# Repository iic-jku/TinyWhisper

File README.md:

# TinyWhisper: An Open-Source Fully-Integrated Multi-Mode Short-Wave Transmitter for Amateur Radio Applications in 130-nm CMOS

(c) 2025-2026 Simon Dorrer* (OE3SDE), Jonathan Hager** (DK7JH), Matthias Jung** (DL9MJ) and Harald Pretl*

*Institute for Integrated Circuits and Quantum Computing, Johannes Kepler University (JKU), Linz, Austria

**Computer Engineering, Julius-Maximilians-Universität, Würzburg, Germany

> [!IMPORTANT]
> This repository requires the [IIC-OSIC-TOOLS](https://github.com/iic-jku/IIC-OSIC-TOOLS) container with tag `2026.11` or later.

> [!TIP]
> This repository is based on the [ihp-sg13g2-ams-chip-template](https://github.com/iic-jku/ihp-sg13g2-ams-chip-template) template repository. For a better understanding of the folder structure, how to use the Makefiles, and how to implement your own designs, it is recommended to go through this [tutorial](https://iic-jku.github.io/ihp-sg13g2-ams-chip-template/index.html).

<p align="center">
  
  <br>
  <em>Die photo of the ihp-sg13cmos TinyWhisper ASIC (2mm x 2mm), taped out in March 2026.</em>
</p>

<p align="center">
  
  <br>
  <em>Chip render of the ihp-sg13cmos TinyWhisper ASIC (2mm x 2mm).</em>
</p>

<p align="center">
  
  <br>
  <em>Render of the TopMetal2 TinyWhisper logo, generated with the tool ArtistIC.</em>
</p>

## Video

Two videos of about 70 seconds introduce TinyWhisper to a general audience, one in English and one in German. Click a poster to play its video, or watch both in the [documentation](https://iic-jku.github.io/TinyWhisper/index.html#sec-video).

<table width="100%">
  <tr>
    <td align="center" width="50%">
      
      <br>
      <em>▶ English, 1:11</em>
    </td>
    <td align="center" width="50%">
      
      <br>
      <em>▶ German, 1:08</em>
    </td>
  </tr>
</table>

## Documentation

The full documentation of the TinyWhisper transmitter is available [here](https://iic-jku.github.io/TinyWhisper/index.html).

Moreover, look into the [`publications/`](https://github.com/iic-jku/TinyWhisper/tree/main/publications) folder for further information.

## Purpose

TinyWhisper demonstrates what is possible with current open-source tools and open-source PDKs, from system design to final tapeout, from packaging to PCB design, and even to a 3D-printed enclosure. It can also be used for:

- Ham radio courses
- University courses
- Regression tests of various open-source tools

## Chip Specifications

| Parameter           | Value                                                                             |
| ------------------- | --------------------------------------------------------------------------------- |
| Technology          | SKY130 \& IHP SG13CMOS (130 nm CMOS)                                              |
| Die Area            | 2000 × 2000 µm (4 mm²)                                                            |
| Core Area           | 1270 × 1270 µm (1.613 mm²)                                                        |
| Clock Frequency     | 56 MHz                                                                            |
| Core Supply Voltage | 1.5 V                                                                             |
| I/O Supply Voltage  | 3.3 V                                                                             |
| Total Pads          | 56 (clock, reset, 6 input, 9 output, 9 bidirectional, 8 analog, 7 VDD, 9 VSS, 3 IOVDD, 3 IOVSS) |
| Packaging           | QFN-48, the 9 VSS and 3 IOVSS pads are downbonded to the exposed pad (package ground) |
| Temperature Range   | -40 °C to +125 °C                                                                 |

## Overview

- Analog Front-End: IQ Modulator
    - 3rd-order multiple-feedback (MFB) low-pass filter
        - Butterworth
        - fc = 400 kHz
        - Barthelemy / Manfredini (B/M) inverter-based OTA
    - Passive CMOS voltage-mode mixer
        - Single-to-differential conversion circuit
        - Simple transmission-gate switch
- Digital Core
    - RISC-V CPU
        - SPI interface for external SRAM extension
        - I²C interface for external peripherals (I/O extender, display, keyboard, etc.)
        - UART interface for connection to PC / Raspberry Pi RP2040 + MicroPython
        - 8 × GPIOs (4 × inputs, one with external interrupt capability, and 4 × outputs)
    - 30-bit iterative CORDIC for sine / cosine generation
        - Adjustable amplitude
        - Adjustable fc, fm, and phim enable different modulation schemes
        - Frequency resolution: df = fclk / (OSR × 2^30), 1.63 mHz at OSR 32
        - Frequency word: fc = 2^30 × OSR × frequency / fclk (30 bit, signed)
    - Delta-Sigma modulator
        - OSR = 32 / 64 / 128 / 256
        - 1st / 2nd order
        - Inversion / exchange of the I/Q channel
    - 25% LO Generation for Mixer
        - LO = fclk / 2, 4, 8 or 16 (28, 14, 7 or 3.5 MHz)
        - Debugging modes (mixer TG always on / off → fully differential measurement of the MFB filter is possible)
    - Debugging features
        - Bidirectional pads: measure DSM / LO output or inject signals externally
        - Analog pads: inject analog IQ modulator signals externally

## Description

TinyWhisper is a compact WSPR transmitter realized with the ihp-sg13cmos PDK. The 2 mm x 2 mm chip operates at a core supply voltage of 1.5 V and an I/O supply voltage of 3.3 V. The chip is [packaged](https://github.com/iic-jku/TinyWhisper/tree/main/ihp130/packaging) in a QFN-48 package. The chip has 56 pads, and its 9 VSS and 3 IOVSS pads are downbonded to the exposed pad of the package. All documentation, presentations, design files, and future updates are publicly available [here](https://github.com/iic-jku/TinyWhisper/tree/main/publications). The block diagram is shown below. A render of the final chip layout is shown above, with the digital part placed on the left side of the chip and the analog part on the right. A custom logo on the topmost metal layer, generated with the tool [ArtistIC](https://arxiv.org/abs/2502.02626), is also shown above. The die photo at the top shows a fabricated chip of the March 2026 tapeout (`SoC4219`), with the TopMetal2 logo on top of the core.

<p align="center">
  
  <br>
  <em>Block diagram of the TinyWhisper ASIC and external RF circuitry.</em>
</p>

### Weak Signal Propagation Reporter

WSPR is a popular digital transmission scheme in amateur radio, specifically designed to study propagation conditions at low transmit power. WSPR transmits a short message containing the callsign, location, and transmit power using 4-FSK modulation (tone spacing 1.46 Hz, symbol duration 0.683 s). Thanks to strong forward error correction (rate 1/2), long ranges can be achieved even at very low transmit power levels (down to 10 mW). Receivers can decode WSPR signals down to -31 dB below the noise floor of a 2500 Hz channel. Received signals are reported to a central [database](https://www.wsprnet.org/drupal/wsprnet/map) via the internet, enabling global analysis of signal propagation.

### Digital Core

The heart of the digital core is a simple multi-cycle embedded processor based on a 32-bit RISC-V architecture running at a clock rate of 56 MHz. By using the RISC-V architecture, the CPU is directly compatible with common compilers, and programs can, for example, be written in C. The program is stored in an external SPI SRAM, from which the CPU fetches its instructions. For communication with peripherals, the chip features I2C and UART interfaces as well as digital GPIO pins that can be freely controlled.

An integrated 30-bit CORDIC algorithm generates the 4-FSK-modulated I/Q baseband signals according to the WSPR protocol. The phase increment of the CORDIC can be configured via software, allowing any frequency to be generated with a resolution of 1.63 mHz at an oversampling ratio of 32. This also enables compensation for frequency errors of the external crystal oscillator. Using a first- or second-order Delta-Sigma (DS) modulator with selectable oversampling (32, 64, 128, or 256), the parallel 30-bit data from the CORDIC is converted into a 1-bit signal that is passed directly to the analog front-end. Additionally, the digital core generates the LO frequencies listed in the table below by dividing the 56 MHz clock by 2, 4, 8 or 16, covering the most common shortwave bands: 28 MHz, 14 MHz, 7 MHz, and 3.5 MHz. The signal lands at the LO plus the IF only in the upper sideband, which the firmware has to select, see [errata TW-E03](https://github.com/iic-jku/TinyWhisper/blob/main/ihp130/doc/errata.md#tw-e03-default-iq-convention-transmits-the-lower-sideband).

| Band | RF Frequency  | LO Frequency | IF (CORDIC) |
| ---- | ------------- | ------------ | ----------- |
| 80m  | 3.568600 MHz  | 3.5 MHz      | 68.600 kHz  |
| 40m  | 7.038600 MHz  | 7 MHz        | 38.600 kHz  |
| 20m  | 14.095600 MHz | 14 MHz       | 95.600 kHz  |
| 10m  | 28.124600 MHz | 28 MHz       | 124.600 kHz |

### Analog Front-End

The analog front-end is an IQ modulator consisting of two third-order multiple-feedback (MFB) low-pass filters with a cutoff frequency of 400 kHz and a Butterworth characteristic. The amplifier core of the MFB filter is based on a Barthelemy / Manfredini (B/M) inverter-based OTA. Two passive voltage-mode mixers are driven by a 25% duty-cycle local oscillator and produce a single-ended RF output signal.

Integrated SPDT switches allow switching between the internal CORDIC/DSM signals and external analog inputs, enabling tests with an external function generator, among other uses.

Since the analog front-end is an IQ modulator, it supports not only WSPR but also other modulation schemes such as FT8, SSB, and CW. Hence, the title "TinyWhisper: An Open-Source Fully-Integrated Multi-Mode Short-Wave Transmitter for Amateur Radio Applications in 130-nm CMOS".

### Outlook

Bare dies of the March 2026 tapeout are back from fabrication, see the die photo at the top. The ASIC is just the beginning of a broader open-hardware project. The next step is to design a [PCB](https://github.com/iic-jku/TinyWhisper/tree/main/pcb) that includes all necessary external components: switchable bandpass filters for each RF band, an RF amplifier, a crystal oscillator as the clock source, external SRAM, voltage regulators for the various supply voltages, a display, controls, an SMA connector for the antenna, and a USB interface for configuration. The packaged chip will be soldered onto this board and then [characterized](https://github.com/iic-jku/TinyWhisper/tree/main/measurements).

Building on this PCB, a compact, 3D-printable [enclosure](https://github.com/iic-jku/TinyWhisper/tree/main/enclosure) is planned that accommodates the board together with a small battery and is robust enough for outdoor use during field tests and SOTA activations.

## ToDo List

The ToDo list can be found in [ToDo.md](https://github.com/iic-jku/TinyWhisper/tree/main/ToDo.md).

## Tapeouts

- [x] TinyWhisper Transmitter (Digital Core + IQ Modulator), IHP130: https://github.com/iic-jku/TinyWhisper/tree/main/ihp130/release and branch `IHP-TO-2026-03`
- [x] RISC-V CPU, GF180 wafer.space: https://github.com/iic-jku/gf180mcu-jku-projects
- [x] WSPR in Hardware without RISC-V CPU (see [archive](https://github.com/iic-jku/TinyWhisper/tree/main/sky130/macros/archive/verilog_TT_11-2025) folder), SKY130 Tiny Tapeout: https://tinytapeout.com/chips/ttsky25b/tt_um_cejmu_wspr
- [x] IQ Modulator, SKY130 Tiny Tapeout: https://tinytapeout.com/chips/ttsky25b/tt_um_TinyWhisper

## Directory Structure

The chip design itself lives in [`ihp130/`](https://github.com/iic-jku/TinyWhisper/tree/main/ihp130), which follows the layout of the [ihp-sg13g2-ams-chip-template](https://github.com/iic-jku/ihp-sg13g2-ams-chip-template). Its own [README](https://github.com/iic-jku/TinyWhisper/tree/main/ihp130/README.md) documents every Makefile target in detail.

<details>
<summary>Show Directory Structure</summary>

```text
📁 TinyWhisper/
├─ 📁 .github/
│  └─ 📁 workflows/
│     ├─ license-check.yml
│     ├─ quarto-publish.yml
│     └─ regression.yml
├─ 📁 doc/
│  ├─ 📁 fig/
│  │  ├─ 📁 funding/
│  │  │  ├─ iic-jku.pdf
│  │  │  ├─ iic-jku.svg
│  │  │  ├─ silicon-austria-labs-logo.pdf
│  │  │  └─ silicon-austria-labs-logo.svg
│  │  ├─ Makefile
│  │  ├─ TinyWhisper_architecture.drawio
│  │  ├─ TinyWhisper_architecture.svg
│  │  ├─ favicon.png
│  │  ├─ fec.svg
│  │  ├─ fec.tex
│  │  ├─ tinywhisper_blockdiagramm.png
│  │  ├─ tinywhisper_bondplan_white.png
│  │  ├─ tinywhisper_die.JPG
│  │  ├─ tinywhisper_top_black.png
│  │  ├─ tinywhisper_top_black_TM2.png
│  │  └─ tinywhisper_top_white.png
│  ├─ 📁 scripts/
│  │  └─ copy_sim_figures.ts
│  ├─ 📁 video/
│  │  ├─ tinywhisper_intro_de.jpg
│  │  ├─ tinywhisper_intro_de.mp4
│  │  ├─ tinywhisper_intro_en.jpg
│  │  └─ tinywhisper_intro_en.mp4
│  ├─ Makefile
│  ├─ _quarto.yml
│  ├─ dashboard.html
│  ├─ index.qmd
│  ├─ references.bib
│  ├─ requirements.txt
│  └─ styles.css
├─ 📁 enclosure/
│  └─ README.md
├─ 📁 ihp130/
│  ├─ 📁 doc/
│  ├─ 📁 flow/
│  │  ├─ 📁 artistic/
│  │  ├─ 📁 final/
│  │  ├─ 📁 librelane/
│  │  └─ 📁 logo/
│  ├─ 📁 ip/
│  │  ├─ 📁 sg13g2_io_custom/
│  │  ├─ 📁 sg13g2_ip__bondpad_70x70/
│  │  ├─ 📁 sg13g2_ip__rfpad_70x70/
│  │  ├─ 📁 sg13g2_ip__ce/
│  │  ├─ 📁 sg13g2_ip__ce_names/
│  │  ├─ 📁 sg13g2_ip__jku/
│  │  └─ 📁 sg13g2_ip__jku_names/
│  ├─ 📁 layout/
│  │  ├─ tinywhisper_top.gds.gz
│  │  └─ tinywhisper_top_logo_fill.gds.gz
│  ├─ 📁 macros/
│  │  ├─ 📁 coupled_resonator_lc_bpf/
│  │  ├─ 📁 iqmod/
│  │  ├─ 📁 riscv/
│  │  ├─ 📁 scripts/
│  │  ├─ Makefile
│  │  └─ README.md
│  ├─ 📁 netlist/
│  │  ├─ 📁 layout/
│  │  ├─ 📁 nl/
│  │  ├─ 📁 pex/
│  │  ├─ 📁 pnl/
│  │  ├─ 📁 schematic/
│  │  └─ 📁 spice/
│  ├─ 📁 packaging/
│  │  ├─ 📁 layout/
│  │  ├─ 📁 render/
│  │  ├─ 📁 scripts/
│  │  ├─ config.yaml
│  │  ├─ README.md
│  │  └─ result.md
│  ├─ 📁 release/
│  │  ├─ 📁 v.1.0.0/
│  │  │  ├─ 📁 doc/
│  │  │  │  └─ README.md
│  │  │  ├─ 📁 gds/
│  │  │  │  └─ SoC4219.gds.gz
│  │  │  └─ 📁 img/
│  │  │     ├─ tinywhisper_die_1.JPG
│  │  │     ├─ tinywhisper_die_2.JPG
│  │  │     ├─ tinywhisper_die_3.JPG
│  │  │     ├─ tinywhisper_top_black.png
│  │  │     └─ tinywhisper_top_white.png
│  │  └─ 📁 v.2.0.0/
│  │     ├─ 📁 gds/
│  │     │  └─ tinywhisper_top_logo_fill.gds.gz
│  │     ├─ 📁 img/
│  │     └─ 📁 netlist/
│  │        ├─ 📁 layout/
│  │        ├─ 📁 pnl/
│  │        └─ 📁 spice/
│  ├─ 📁 render/
│  │  ├─ 📁 blender/
│  │  └─ 📁 img/
│  │     ├─ tinywhisper_top_black.png
│  │     ├─ tinywhisper_top_librelane.png
│  │     └─ tinywhisper_top_white.png
│  ├─ 📁 rtl/
│  │  ├─ tinywhisper_core.sv
│  │  └─ tinywhisper_top.sv
│  ├─ 📁 schematic/
│  │  └─ 📁 xschem/
│  │     ├─ tinywhisper.sch
│  │     ├─ tinywhisper.sym
│  │     ├─ tinywhisper_top.sch
│  │     ├─ tinywhisper_top.sym
│  │     ├─ tinywhisper_top_pex.sym
│  │     └─ xschemrc
│  ├─ 📁 scripts/
│  │  ├─ add_logo_fill.sh
│  │  ├─ add_rectangle.py
│  │  └─ check_pex_ports.py
│  ├─ 📁 testbenches/
│  │  ├─ 📁 cocotb/
│  │  └─ 📁 xschem/
│  │     └─ 📁 plot_simulations/
│  ├─ 📁 verification/
│  │  ├─ 📁 drc/
│  │  ├─ 📁 lvs/
│  │  └─ 📁 reports/
│  ├─ Makefile
│  └─ README.md
├─ 📁 LICENSES/
│  ├─ Apache-2.0.txt
│  ├─ LicenseRef-EUROPRACTICE.txt
│  ├─ MIT.txt
│  └─ SHL-2.1.txt
├─ 📁 measurements/
│  └─ README.md
├─ 📁 pcb/
│  ├─ 📁 lib/
│  ├─ 📁 render/
│  ├─ README.md
│  ├─ tinywhisper_dev_board.kicad_pcb
│  ├─ tinywhisper_dev_board.kicad_pro
│  └─ tinywhisper_dev_board.kicad_sch
├─ 📁 publications/
│  ├─ EasterHegg_04042026.pdf
│  ├─ QSP100_Open-Source-Chip-Design.pdf
│  └─ README.md
├─ 📁 sky130/
│  └─ 📁 macros/
│     ├─ 📁 archive/
│     ├─ 📁 iqmod/
│     └─ 📁 riscv/
├─ 📁 software/
│  ├─ 📁 c_toolchain/
│  ├─ generate_tests.py
│  ├─ program_fpga_uart.py
│  ├─ README.md
│  ├─ test_wspr.py
│  └─ wspr.py
├─ .designinit
├─ .gitattributes
├─ .gitignore
├─ .gitmodules
├─ CITATION.cff
├─ LICENSE
├─ README.md
├─ REUSE.toml
└─ ToDo.md
```

</details>

## Cite This Work

```
@software{2026_TinyWhisper,
	author = {Dorrer, Simon and Hager, Jonathan and Jung, Matthias and Pretl, Harald},
	month = apr,
    year = {2026},
	title = {{GitHub Repository for TinyWhisper: An Open-Source Fully-Integrated Multi-Mode Short-Wave Transmitter for Amateur Radio Applications in 130-nm CMOS}},
	url = {https://github.com/iic-jku/TinyWhisper},
	doi = {10.5281/zenodo.20004085}
}
```

## Acknowledgements

Thanks to Chance Reimer for providing an open source [I2C module](https://github.com/chance189/I2C_Master) and to Ben Marshall for providing a [UART implementation](https://github.com/ben-marshall/uart).

This project is funded by the JKU/SAL [IWS Lab](https://research.jku.at/de/projects/jku-lit-sal-intelligent-wireless-systems-lab-iws-lab/), a collaboration of [Johannes Kepler University](https://jku.at) and [Silicon Austria Labs](https://silicon-austria-labs.com).

<table width="100%">
  <tr>
    <td align="left" width="50%">
      
    </td>
    <td align="right" width="50%">
      
    </td>
  </tr>
</table>

## License

Licensed under the **Solderpad Hardware License v2.1**, see [`LICENSE`](LICENSE).

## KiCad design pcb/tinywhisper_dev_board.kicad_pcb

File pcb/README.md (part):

# TinyWhisper dev board

KiCad 10 project of the bring-up board for SoC4219, the first TinyWhisper silicon, in its open-molded QFN-48.
Revision 0.1 covers the digital side completely and gives the RF side debug access only: the four RF outputs joined into a 1 kΩ load and an SMA for a spectrum analyzer, with no band-pass filter, no band switching and no power amplifier.
Every board condition of [`ihp130/doc/errata.md`](../ihp130/doc/errata.md) is built in and cited as `TW-Exx`. [`measurements/README.md`](../measurements/README.md) is the bring-up protocol for this board.

## Block diagram

The sections below give each block's parts and values. `Exx` in the diagram is the errata entry `TW-Exx`.

## Files

| File | Contents |
| --- | --- |
| `tinywhisper_dev_board.kicad_pro` | Project: net classes (`Default`, `Power`), design rules, track and via presets |
| `tinywhisper_dev_board.kicad_sch` | Root sheet: chip, decoupling, straps for the two bond plans, mechanics |
| `power.kicad_sch` | 5 V from the Pico, 3.3 V board rail, `IOVDD` with its supervisor, `VDD` |
| `host.kicad_sch` | Raspberry Pi Pico H, 56 MHz clock, reset flip-flop, UART, links to the chip |
| `memory.kicad_sch` | PSRAM and the chip-side bus buffers |
| `user.kicad_sch` | Buttons, LEDs, I2C, GPIO header, monitor pads |
| `analog.kicad_sch` | External analog inputs, RF debug output |
| `tinywhisper_dev_board.kicad_pcb` | Board, revision 0.1 |
| `tinywhisper_dev_board.kicad_dru` | Custom rules: the stricter value of JLCPCB and Aisler per rule, plus house rules |
| `lib/` | Chip symbol, Pico H symbol, QFN-48 land pattern, Pico socket, SMA and the board-only logos |
| `render/` | Renders of the board |
| `block_diagram.svg` | Block diagram of revision 0.1, drawn separately from the schematic: update it when a block changes |

Stock parts use the KiCad 10 libraries, and their 3D models resolve through `${KICAD10_3DMODEL_DIR}`.

## Chip

| Item | Value |
| --- | --- |
| Package | QP Technologies `QP-QFN48-7MM-0.50MM` (dwg 500363 rev A), the EUROPRACTICE `OP_QFN48`: 7 × 7 mm, 0.5 mm pitch, 0.23 mm leads, 5.1 mm exposed pad |
| Land pattern | 0.25 mm lands from 3.0 to 4.05 mm off the centre (0.55 mm toe for an iron), 5.1 mm exposed pad with a 1.0 mm plated hole for soldering from the bottom |
| Ground | The exposed pad is the only ground of the die: all 9 `VSS` and 3 `IOVSS` pads are downbonded to the paddle, and the leads 15, 27, 34 and 46 are bonded to it ([`ihp130/packaging/config.yaml`](../ihp130/packaging/config.yaml)). Eight vias in the pad tie it to all four layers. |
| Orientation | Turned by 270°: pins 1 to 12 (clock, reset, SPI, I2C, UART) face the Pico and the PSRAM, pins 25 to 36 (analog inputs, RF) face the RF SMA |
| Decoupling | 100 nF 0603 per supply pin on the bottom side, `C101` to `C107` for the `VDD` pins 8, 14, 20, 28, 33, 41, 47 and `C108` to `C110` for the `IOVDD` pins 7, 13, 48. Each supply pin has a fixed escape on `F.Cu` to a via in the supply pad of its own capacitor, 4.75 mm from the chip centre, and each capacitor's ground pad a via on the same axis. Pins 7 and 47 sit next to the supply pins 8 and 48, so their escapes run past those vias to `C108` and `C107` at 9.2 mm. Pin 14 reaches `VDD` through the strap `R101`, with `C102` beside it. |
| Escapes | Every other signal pin has a straight 0.25 mm stub out to 5.3 mm from the centre, so the autorouter starts outside the ring of supply vias. The vias on the pin axes are 0.45 mm with a 0.25 mm drill and the escapes 0.25 mm wide near the chip, so a neighbouring escape passes a via at the 0.15 mm clearance. |

Pins 14 and 15 were swapped in the bond plan of 2026-11-11 (TW-D03). The board straps both variants:

| Bond plan | Pin 14 | Pin 15 | Fit |
| --- | --- | --- | --- |
| 2026-11-11 (`ihp130/packaging/result.md`, default) | `VDD` | `IOVSS` lead to the cavity | `R101`, `R103` |
| Before 2026-11-11 | `IOVSS` | `VDD` | `R102`, `R104` instead |

Check one loose part before soldering: pin 15 against the exposed pad reads about 0 Ω for the plan of 2026-11-11. Step 1 of [`measurements/README.md`](../measurements/README.md) has the full check.

## Supplies

| Rail | Source | Load |
| --- | --- | --- |
| `+5V` | Pico `VBUS` (pin 40) through the ferrite `FB201`, so the Pico's USB powers the board | `U201` |
| `+3V3` | `U201` AP2112K-3.3, 600 mA | Pico interface, PSRAM, bus buffers, oscillator, reset flip-flop, OLED, `IOVDD`, `VDD` regulator |
| `IOVDD` | `+3V3` through the current jumper `JP201`, voltage header `J201` | Chip I/O ring (3 pins), the pull-ups on chip inputs |
| `VDD` | `U203` LP5907MFX-1.5 from `+3V3`, through the current jumper `JP202`, voltage header `J202` | Chip core (7 pins): CPU and IQ modulator share it (TW-E28) |

Sequencing (TW-E31): the supervisor `U202` (TPS3839K33) raises `PG_IO` 200 ms after `IOVDD` exceeds 2.93 V. `PG_IO` enables `U203`, so `VDD` follows `IOVDD`, and the LP5907 output discharge pulls `VDD` down first when `IOVDD` drops. `PG_IO` also clears the reset flip-flop, so `rst_n` stays low without `IOVDD`.
The LP5907 sees 6.4 µF on its output (`C208`, `C209` and the seven `VDD` decoupling capacitors), within its 10 µF limit.

Pull `JP201` or `JP202` to measure a current with an ammeter, or to feed a current-limited bench supply into pin 2 of the jumper (the chip side) with `GND` on pin 2 of `J201` or `J202`. With the bench supply, bring up `IOVDD` before `VDD`.

## Host

A Raspberry Pi Pico H (RP2040) on two 1x20 sockets loads the program, owns reset and the PSRAM bus, and bridges USB to the chip's UART, as the RP2040 does on pico-ice.

| Pico | Net | Function |
| --- | --- | --- |
| `GP0` | `UART_RX` through `R310` 1 kΩ | Chip `rx` (pin 11), 10 kΩ pull-up `R311` to `IOVDD` (TW-E29) |
| `GP1` | `UART_TX` through `R312` 1 kΩ | Chip `tx` (pin 12) |
| `GP2` | `BUS_PICO`, 10 kΩ pull-up `R326` | High: the Pico owns the PSRAM and the chip-side buffers are off (TW-E02) |
| `GP3` | `RST_REQ_N` through `R307` 1 kΩ, 10 kΩ pull-down `R308` | Reset request into the flip-flop, low until the firmware releases it |
| `GP4`, `GP5` | `SDA`, `SCL` through `R321`, `R322` (not fitted) | I2C sniffer, the chip stays the only master (TW-E14) |
| `GP6` to `GP9` | `gpio_in[0..3]` through 1 kΩ (`R313` to `R316`) | Drive the chip inputs, `gpio_in[0]` is the external interrupt (TW-E24) |
| `GP10` to `GP13` | `gpio_out[0..3]` through 1 kΩ (`R317` to `R320`) | Read the chip outputs |
| `GP14` | `CLK_OE`, 10 kΩ pull-up `R301` | Oscillator enable, on while the pin is an input |
| `GP16` to `GP19` | `PSRAM_SO` (`R411`), `PSRAM_CE_N` (`R408`), `PSRAM_SCLK` (`R409`), `PSRAM_SI` (`R410`), 100 Ω each | SPI0 to the PSRAM: MISO, CS, SCK, MOSI |
| `GP26` | `VDD` through `R323` 1 kΩ | ADC readback of `VDD` |
| `GP27` | `IOVDD / 2` (`R324`, `R325`) | ADC readback of `IOVDD` |
| `GP15`, `GP20` to `GP22`, `GP28` | `J303` | Spare |
| `RUN` | `SW301` | Pico reset |

Loading order: with `BUS_PICO` high the Pico writes the program into the PSRAM over SPI0 (150 µs after power-up at the earliest), checks `VDD` on `GP26`, sets `BUS_PICO` low and raises `RST_REQ_N`. The flip-flop then releases `rst_n` on the next rising clock edge.

## Clock and reset

- `X301` is a 56 MHz SiT8008 CMOS oscillator at 3.3 V (programmable family, any frequency to order). `R304` (0 Ω, fitted) selects it. For a generator, fit `R305` instead and drive the SMA `J301` with a 3.3 V CMOS square wave. `R303` (49.9 Ω, not fitted) terminates a generator that needs it.
- The clock passes `R306` (33 Ω) to pin 1 and clocks the reset flip-flop `U301` (74AUP1G74 at 3.3 V, clock input high at 2.0 V or more). On 10 m the clock duty sets the I/Q balance (TW-E27): trim it with a generator on `J301`.
- `U301` releases `rst_n` (through `R309`, 33 Ω) synchronous to the clock (TW-E25), clears it while `PG_IO` is low (TW-E31), and `SW302` (RESET) pulls its D input low.
- Test points: `TP301` on `CLK` at the chip, `TP302` on `RST_N`.

## Memory

The CPU fetches from `U401`, an APS6404L-3SQR 64 Mbit SPI PSRAM at 3.3 V.
The chip's `si`, `sclk` and `sram_ce` drive even in reset and `sclk` runs at 28 MHz without pause (TW-E02), so they reach the PSRAM through the tri-state buffers `U403` (`si`), `U402` (`sclk`) and the inverting `U404` (`sram_ce` is active high, TW-E01), all enabled while `BUS_PICO` is low. `R401` keeps `CE#` high while nobody drives it, and `R405` keeps the inverter input low with the chip unpowered.
The series resistors `R402` to `R404` and `R406` (33 Ω) sit at the chip pins, and `R407` pulls `so` up (TW-E29).

## User I/O

| Part | Function |
| --- | --- |
| `SW501` to `SW504` | Buttons on `gpio_in[0..3]`, 1 kΩ to `IOVDD` (`R513` to `R516`), 10 kΩ pull-downs (`R501` to `R504`, TW-E29) |
| `D501` to `D504` | LEDs on `gpio_out[0..3]` through 1 kΩ (`R505` to `R508`) |
| `J501` | I2C display module: 1 `GND`, 2 `+3V3`, 3 `SCL`, 4 `SDA`. The chip drives `SDA` high push-pull, so 100 Ω in series (`R509`, `R510`) and 4.7 kΩ pull-ups to `IOVDD` (`R511`, `R512`). Fast-mode slaves that never stretch the clock (TW-E14, TW-E15). |
| `J302` | UART: 1 `tx` (chip output), 2 `rx` (chip input), 3 `GND`. The host sends 2 stop bits (TW-E07). |
| `J303` | Spare Pico pins: 1 `+3V3`, 2 `GP15`, 3 `GP20`, 4 `GP21`, 5 `GP22`, 6 `GP28`, 7 `GND` |

`J502` (GPIO) and `J503` (monitor pads) have the signals on the odd pins and `GND` on every even pin:

| Pin | `J502` | `J503` |
| --- | --- | --- |
| 1 | `gpio_in[0]` | `lo_I` (pin 38) |
| 3 | `gpio_in[1]` | `lo_Ix` (pin 37) |
| 5 | `gpio_in[2]` | `lo_Q` (pin 23) |
| 7 | `gpio_in[3]` | `lo_Qx` (pin 24) |
| 9 | `gpio_out[0]` through 100 Ω | `ds_I_p` (pin 40) |
| 11 | `gpio_out[1]` through 100 Ω | `ds_I_n` (pin 39) |
| 13 | `gpio_out[2]` through 100 Ω | `ds_Q_p` (pin 21) |
| 15 | `gpio_out[3]` through 100 Ω | `ds_Q_n` (pin 22) |

The eight monitor pads drive 30 mA at the LO rate whenever the internal LO runs (TW-E26). Each reaches `J503` through 100 Ω at the chip (`R517` to `R524`) and has a 100 kΩ pull-down at the pin (`R525` to `R532`), because the reset value of `FREQ_STATUS` makes them inputs (TW-E04).

## Analog inputs and RF debug output

- `J601` brings out the four external analog inputs (1 `vinp_I`, 3 `vinn_I`, 5 `vinp_Q`, 7 `vinn_Q`, even pins `GND`). Each passes 1 kΩ (`R601` to `R604`) and is biased to `VCM` = 0.75 V through 100 kΩ (`R605` to `R608`, divider `R609`, `R610` from `VDD`). Keep them within 0 to 1.5 V and never drive them with the chip unpowered: their clamps go to `IOVDD` (TW-E30).
- The four RF outputs (pins 29 to 32) are joined through the 0 Ω links `R611` to `R614` into `RF_SUM` (TW-E03, test point `TP601`). `C602` (100 nF) blocks their 0.75 V DC level (TW-E30), and `R615` (953 Ω) feeds the end-launch SMA `J602`. With a 50 Ω analyzer the outputs see 1003 Ω, and the analyzer reads 26.0 dB below the voltage at `RF_SUM`. Remove three links to measure one output alone.
- There is no filter on this board: the switching mixer puts power at odd LO harmonics. Use `J602` only into an analyzer or through an external low-pass filter.

## Assembly

All passives are 0603 or larger and all ICs leaded or with a land toe (SOT-23, SSOP-8, SOIC-8, the QFN-48 with extended lands), so the board can be soldered by hand. Connectors, buttons and test points are through-hole.
The QFN-48 exposed pad is soldered from the bottom through its 1.0 mm hole, or on a hot plate. The decoupling capacitors `C101` to `C110` sit on the bottom side under the chip, so solder the chip first.
The Pico H sits on two 1x20 sockets (Sullins PPTC201LFBN-RC), so it can be replaced and its own pins stay free.

## Markings

- Layer marker below the spare Pico header: `TOP` (`F.Cu`) and `2` (`In1.Cu`) read from the top, `3` (`In2.Cu`) and `BOT` (`B.Cu`), mirrored, from the bottom, in rule areas that forbid only the pour.
- Write-on field for the part number above the title.
- Every connector, jumper, button and test point is named by function. The supply jumpers read `IOVDD I` and `VDD I`, their voltage headers `U`, and `TP601` (`RF_SUM`) reads `RF`.
- JKU, ESD and WEEE logos on the bottom silkscreen, as board-only footprints (no symbol, not in the BOM or the position files).

## Fabrication

The board fits both JLCPCB and Aisler on one rule set, as the SPARX probe board: per rule the stricter value of the two.

| Rule | Value |
| --- | --- |
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
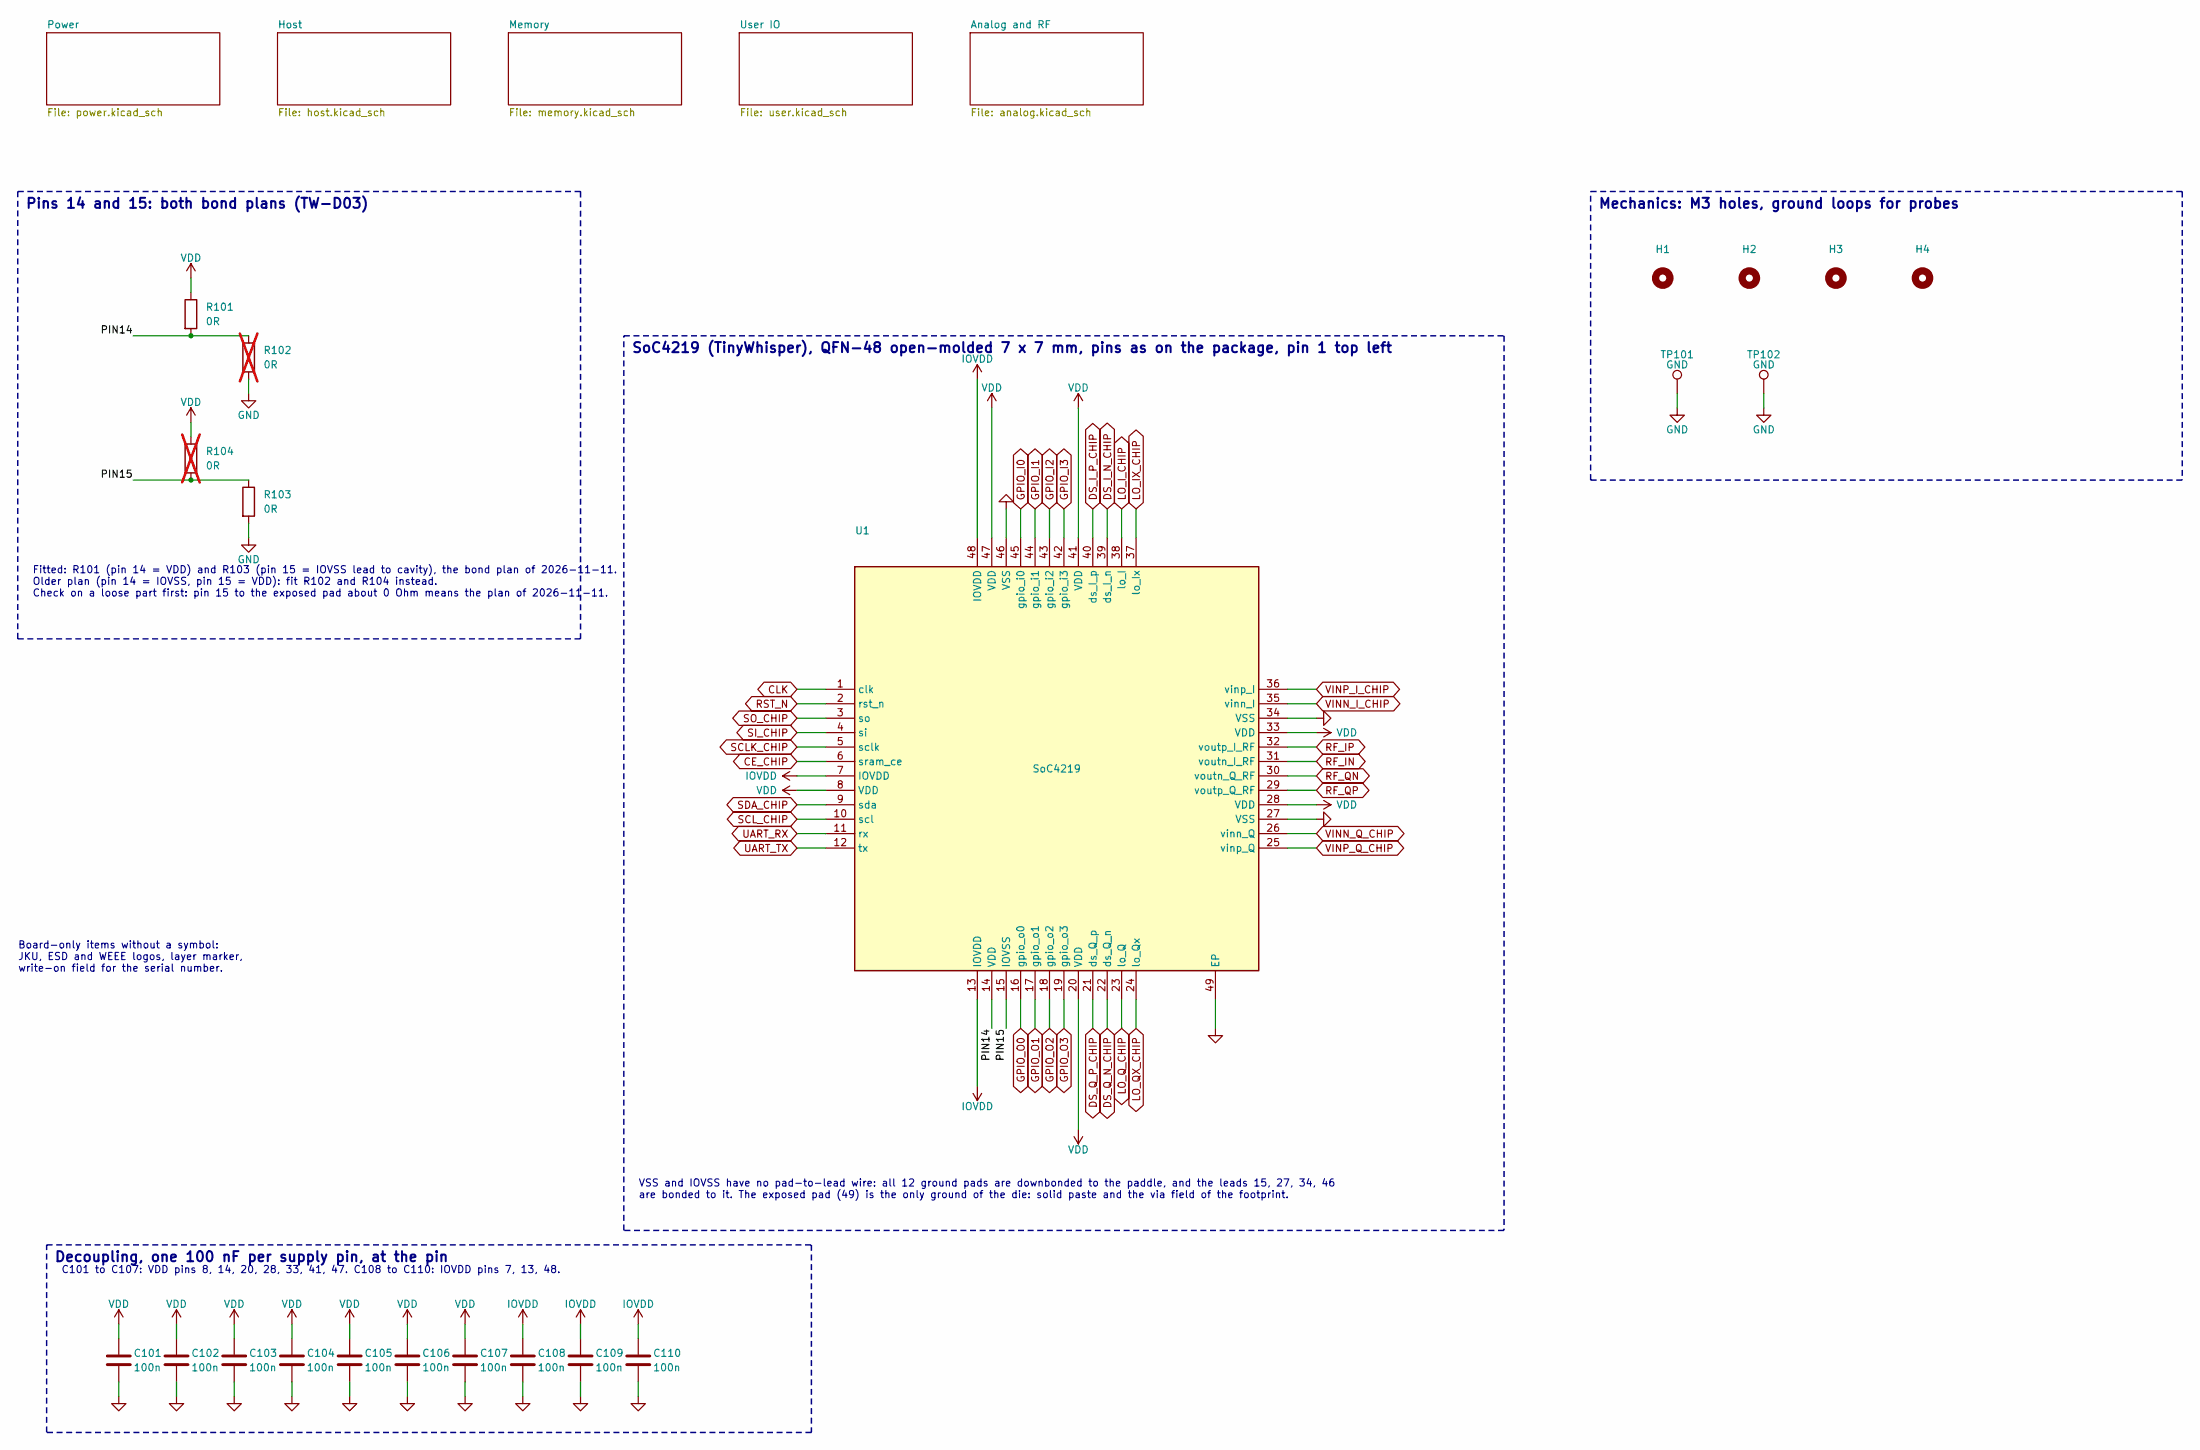
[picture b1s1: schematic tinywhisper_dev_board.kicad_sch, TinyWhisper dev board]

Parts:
C101, C102, C103, C104, C105, C106, C107, C108, C109, C110: 100n; C_0603_1608Metric_Pad1.08x0.95mm_HandSolder; MPN CL10B104KB8NNNC
H1, H2, H3, H4: MountingHole_M3; MountingHole_3.2mm_M3
R101, R103: 0R; R_0603_1608Metric_Pad0.98x0.95mm_HandSolder; MPN RC0603JR-070RL
R102, R104: 0R; R_0603_1608Metric_Pad0.98x0.95mm_HandSolder; MPN RC0603JR-070RL; not fitted
TP101, TP102: GND; TestPoint_Keystone_5000-5004_Miniature; MPN 5000
U1: SoC4219; QFN-48-1EP_7x7mm_P0.5mm_EP5.1x5.1mm_OpenPak_HandSolder

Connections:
/PIN14: R101.2, R102.1, U1.14 (VDD)
/PIN15: R103.1, R104.2, U1.15 (IOVSS)
CE_CHIP: U1.6 (sram_ce); also elsewhere on the board
CLK: U1.1 (clk); also elsewhere on the board
DS_I_N_CHIP: U1.39 (ds_I_n); also elsewhere on the board
DS_I_P_CHIP: U1.40 (ds_I_p); also elsewhere on the board
DS_Q_N_CHIP: U1.22 (ds_Q_n); also elsewhere on the board
DS_Q_P_CHIP: U1.21 (ds_Q_p); also elsewhere on the board
GND: C101.2, C102.2, C103.2, C104.2, C105.2, C106.2, C107.2, C108.2, C109.2, C110.2, R102.2, R103.2, TP101.1, TP102.1, U1.27 (VSS), U1.34 (VSS), U1.46 (VSS), U1.49 (EP); also elsewhere on the board
GPIO_I0: U1.45 (gpio_i0); also elsewhere on the board
GPIO_I1: U1.44 (gpio_i1); also elsewhere on the board
GPIO_I2: U1.43 (gpio_i2); also elsewhere on the board
GPIO_I3: U1.42 (gpio_i3); also elsewhere on the board
GPIO_O0: U1.16 (gpio_o0); also elsewhere on the board
GPIO_O1: U1.17 (gpio_o1); also elsewhere on the board
GPIO_O2: U1.18 (gpio_o2); also elsewhere on the board
GPIO_O3: U1.19 (gpio_o3); also elsewhere on the board
IOVDD: C108.1, C109.1, C110.1, U1.7 (IOVDD), U1.13 (IOVDD), U1.48 (IOVDD); also elsewhere on the board
LO_IX_CHIP: U1.37 (lo_Ix); also elsewhere on the board
LO_I_CHIP: U1.38 (lo_I); also elsewhere on the board
LO_QX_CHIP: U1.24 (lo_Qx); also elsewhere on the board
LO_Q_CHIP: U1.23 (lo_Q); also elsewhere on the board
RF_IN: U1.31 (voutn_I_RF); also elsewhere on the board
RF_IP: U1.32 (voutp_I_RF); also elsewhere on the board
RF_QN: U1.30 (voutn_Q_RF); also elsewhere on the board
RF_QP: U1.29 (voutp_Q_RF); also elsewhere on the board
RST_N: U1.2 (rst_n); also elsewhere on the board
SCLK_CHIP: U1.5 (sclk); also elsewhere on the board
SCL_CHIP: U1.10 (scl); also elsewhere on the board
SDA_CHIP: U1.9 (sda); also elsewhere on the board
SI_CHIP: U1.4 (si); also elsewhere on the board
SO_CHIP: U1.3 (so); also elsewhere on the board
UART_RX: U1.11 (rx); also elsewhere on the board
UART_TX: U1.12 (tx); also elsewhere on the board
VDD: C101.1, C102.1, C103.1, C104.1, C105.1, C106.1, C107.1, R101.1, R104.1, U1.8 (VDD), U1.20 (VDD), U1.28 (VDD), U1.33 (VDD), U1.41 (VDD), U1.47 (VDD); also elsewhere on the board
VINN_I_CHIP: U1.35 (vinn_I); also elsewhere on the board
VINN_Q_CHIP: U1.26 (vinn_Q); also elsewhere on the board
VINP_I_CHIP: U1.36 (vinp_I); also elsewhere on the board
VINP_Q_CHIP: U1.25 (vinp_Q); also elsewhere on the board

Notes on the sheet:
SoC4219 (TinyWhisper), QFN-48 open-molded 7 x 7 mm, pins as on the package, pin 1 top left
VSS and IOVSS have no pad-to-lead wire: all 12 ground pads are downbonded to the paddle, and the leads 15, 27, 34, 46 are bonded to it. The exposed pad (49) is the only ground of the die: solid paste and the via field of the footprint.
Pins 14 and 15: both bond plans (TW-D03)
Fitted: R101 (pin 14 = VDD) and R103 (pin 15 = IOVSS lead to cavity), the bond plan of 2026-11-11. Older plan (pin 14 = IOVSS, pin 15 = VDD): fit R102 and R104 instead. Check on a loose part first: pin 15 to the exposed pad about 0 Ohm means the plan of 2026-11-11.
Decoupling, one 100 nF per supply pin, at the pin
C101 to C107: VDD pins 8, 14, 20, 28, 33, 41, 47. C108 to C110: IOVDD pins 7, 13, 48.
Mechanics: M3 holes, ground loops for probes
Board-only items without a symbol: JKU, ESD and WEEE logos, layer marker, write-on field for the serial number.

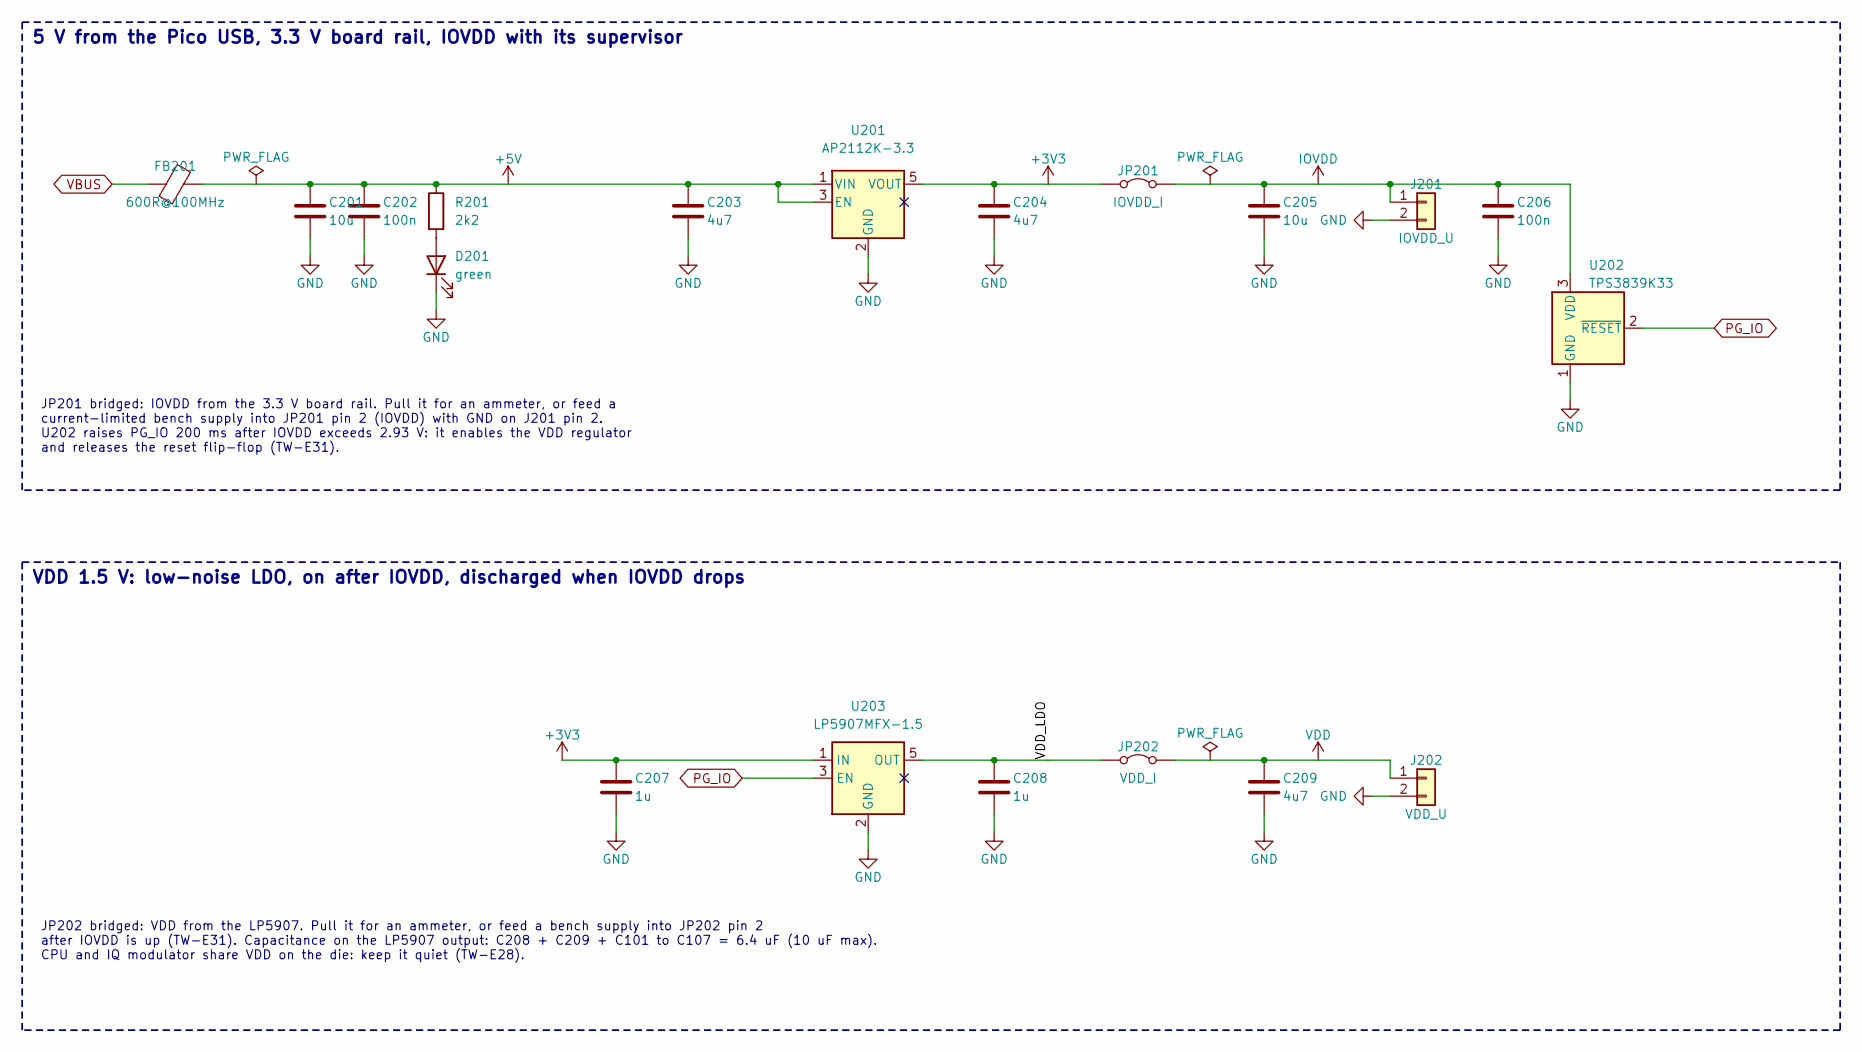
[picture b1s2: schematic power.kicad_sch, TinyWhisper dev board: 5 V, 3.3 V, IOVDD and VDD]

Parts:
C201: 10u; C_1206_3216Metric_Pad1.33x1.80mm_HandSolder; MPN GRM31CR71E106KA12L
C202, C206: 100n; C_0603_1608Metric_Pad1.08x0.95mm_HandSolder; MPN CL10B104KB8NNNC
C203, C204, C209: 4u7; C_0805_2012Metric_Pad1.18x1.45mm_HandSolder; MPN CL21B475KOFNNNE
C205: 10u; C_0805_2012Metric_Pad1.18x1.45mm_HandSolder; MPN CL21A106KOQNNNE
C207, C208: 1u; C_0603_1608Metric_Pad1.08x0.95mm_HandSolder; MPN CL10B105KO8NNNC
D201: green; LED_0603_1608Metric_Pad1.05x0.95mm_HandSolder; MPN APT1608LZGCK
FB201: 600R@100MHz; L_0603_1608Metric_Pad1.05x0.95mm_HandSolder; MPN BLM18KG601SN1D
J201: IOVDD_U; PinHeader_1x02_P2.54mm_Vertical
J202: VDD_U; PinHeader_1x02_P2.54mm_Vertical
JP201: IOVDD_I; PinHeader_1x02_P2.54mm_Vertical
JP202: VDD_I; PinHeader_1x02_P2.54mm_Vertical
R201: 2k2; R_0603_1608Metric_Pad0.98x0.95mm_HandSolder; MPN RC0603FR-072K2L
U201: AP2112K-3.3; SOT-23-5; MPN AP2112K-3.3TRG1
U202: TPS3839K33; SOT-23; MPN TPS3839K33DBZR
U203: LP5907MFX-1.5; SOT-23-5; MPN LP5907MFX-1.5/NOPB

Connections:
+3V3: C204.1, C207.1, JP201.1 (A), U201.5 (VOUT), U203.1 (IN); also elsewhere on the board
+5V: C201.1, C202.1, C203.1, FB201.2, R201.1, U201.1 (VIN), U201.3 (EN)
/Power/VDD_LDO: C208.1, JP202.1 (A), U203.5 (OUT)
GND: C201.2, C202.2, C203.2, C204.2, C205.2, C206.2, C207.2, C208.2, C209.2, D201.1 (K), J201.2, J202.2, U201.2 (GND), U202.1 (GND), U203.2 (GND); also elsewhere on the board
IOVDD: C205.1, C206.1, J201.1, JP201.2 (B), U202.3 (VDD); also elsewhere on the board
unnamed: D201.2 (A), R201.2
PG_IO: U202.2 (~RESET), U203.3 (EN); also elsewhere on the board
VBUS: FB201.1; also elsewhere on the board
VDD: C209.1, J202.1, JP202.2 (B); also elsewhere on the board

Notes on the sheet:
5 V from the Pico USB, 3.3 V board rail, IOVDD with its supervisor
JP201 bridged: IOVDD from the 3.3 V board rail. Pull it for an ammeter, or feed a current-limited bench supply into JP201 pin 2 (IOVDD) with GND on J201 pin 2. U202 raises PG_IO 200 ms after IOVDD exceeds 2.93 V: it enables the VDD regulator and releases the reset flip-flop (TW-E31).
VDD 1.5 V: low-noise LDO, on after IOVDD, discharged when IOVDD drops
JP202 bridged: VDD from the LP5907. Pull it for an ammeter, or feed a bench supply into JP202 pin 2 after IOVDD is up (TW-E31). Capacitance on the LP5907 output: C208 + C209 + C101 to C107 = 6.4 uF (10 uF max). CPU and IQ modulator share VDD on the die: keep it quiet (TW-E28).

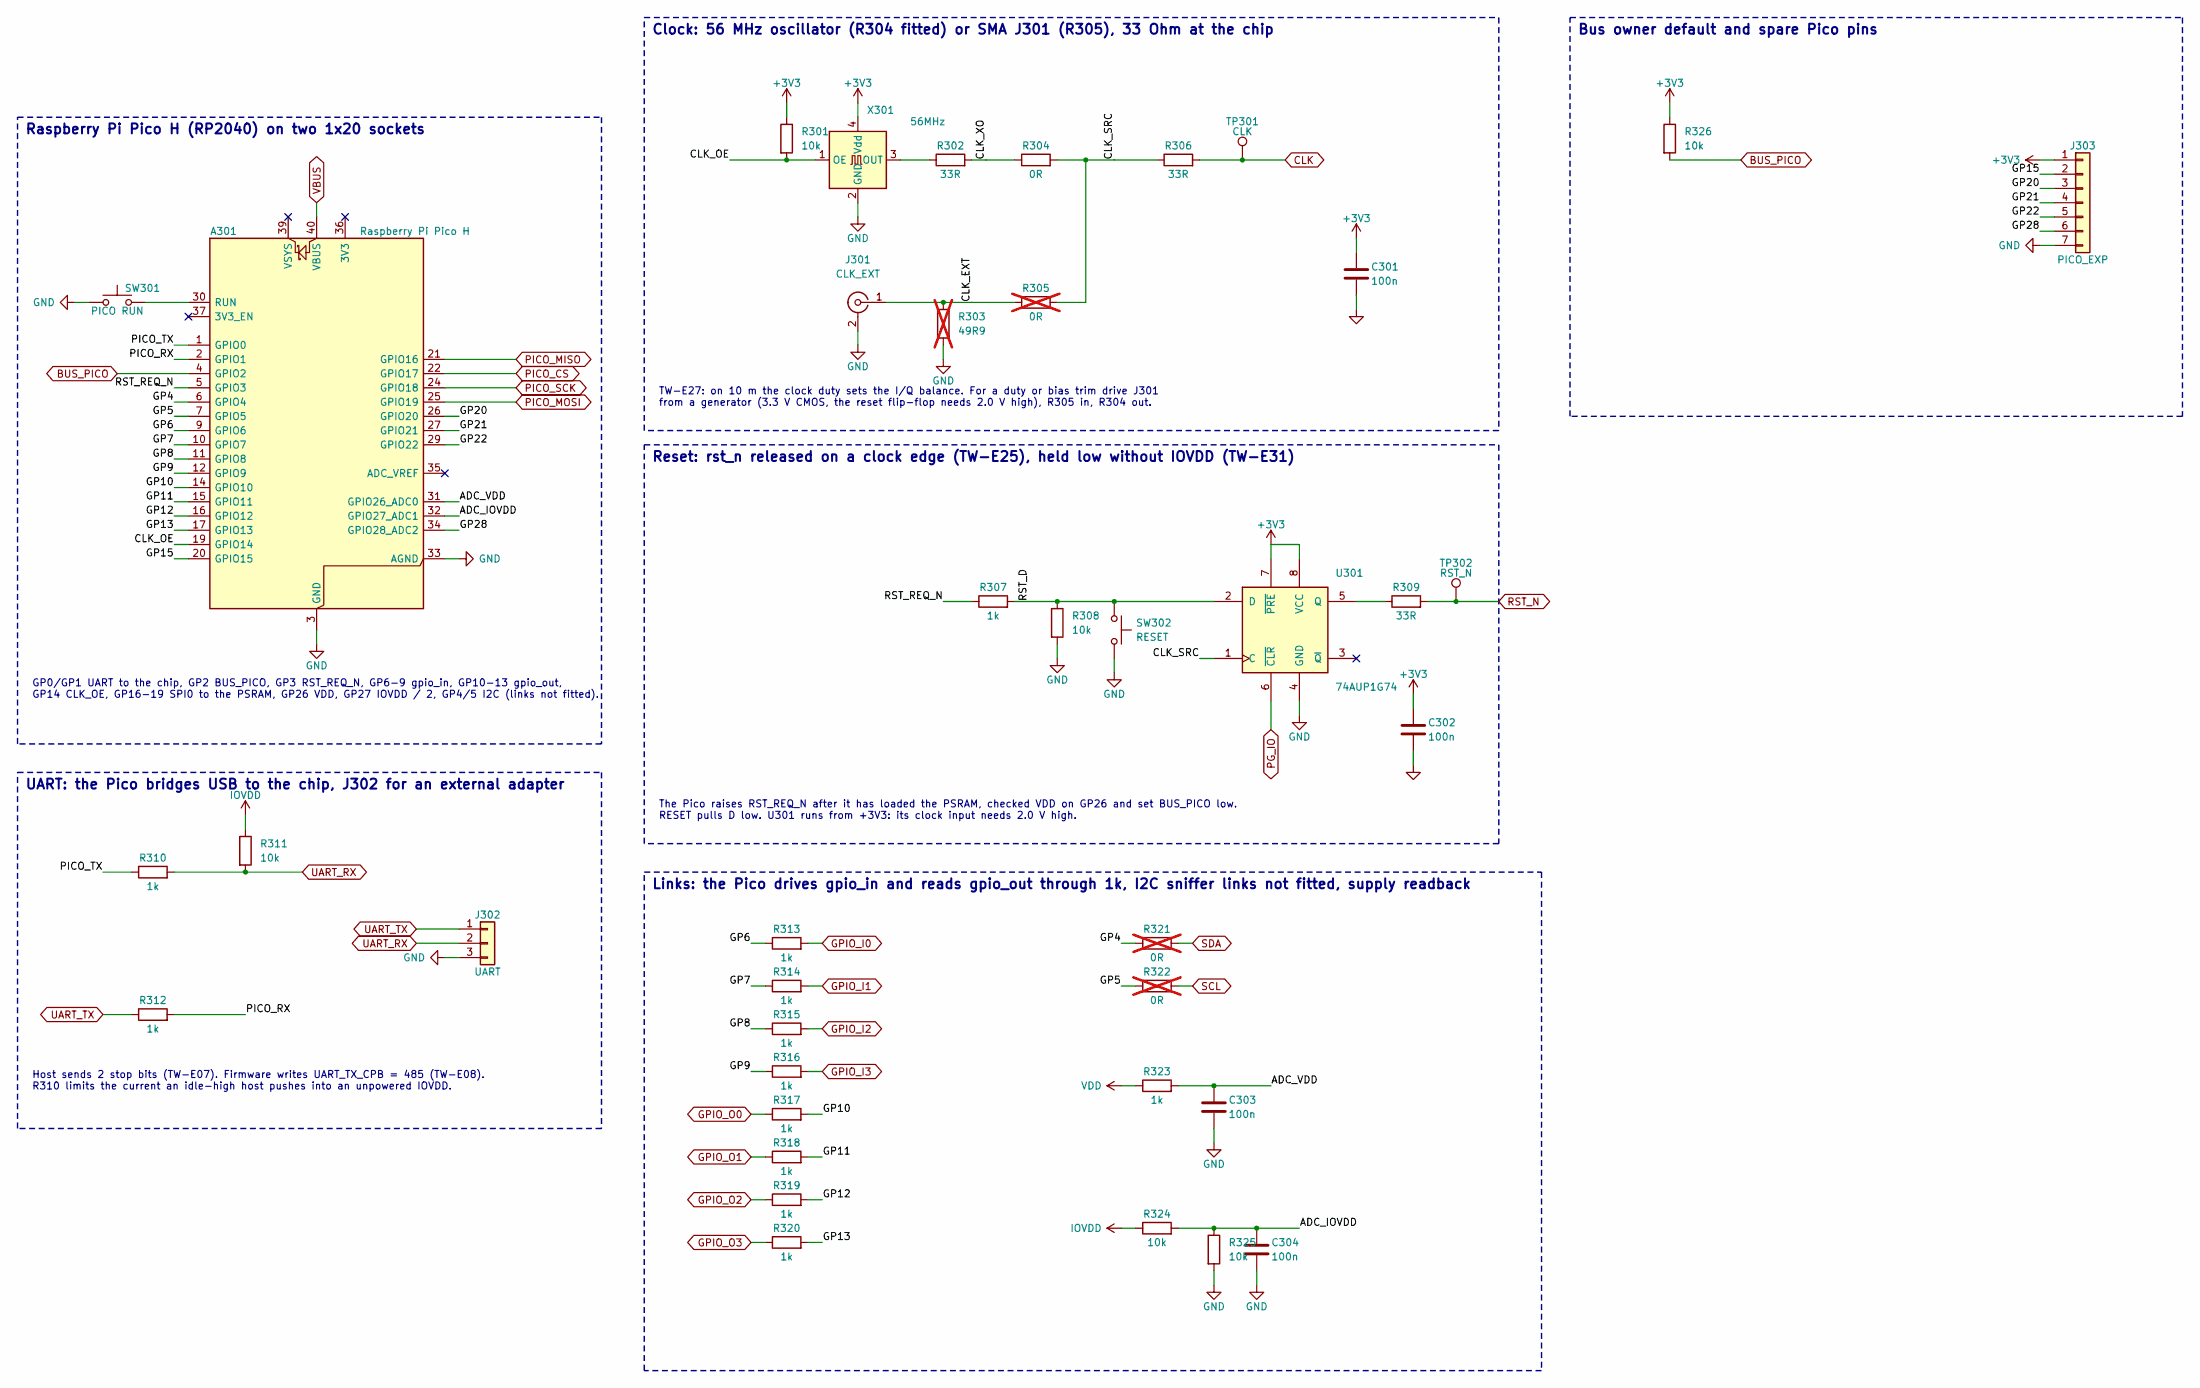
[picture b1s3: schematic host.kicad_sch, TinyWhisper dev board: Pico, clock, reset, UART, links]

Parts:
A301: Raspberry Pi Pico H; RaspberryPi_Pico_H_Sockets; MPN SC0917
C301, C302, C303, C304: 100n; C_0603_1608Metric_Pad1.08x0.95mm_HandSolder; MPN CL10B104KB8NNNC
J301: CLK_EXT; SMA_Cinch_142-0761-881_EndLaunch; MPN 142-0761-881
J302: UART; PinHeader_1x03_P2.54mm_Vertical
J303: PICO_EXP; PinHeader_1x07_P2.54mm_Vertical
R301, R308, R311, R324, R325, R326: 10k; R_0603_1608Metric_Pad0.98x0.95mm_HandSolder; MPN RC0603FR-0710KL
R302, R306, R309: 33R; R_0603_1608Metric_Pad0.98x0.95mm_HandSolder; MPN RC0603FR-0733RL
R303: 49R9; R_0603_1608Metric_Pad0.98x0.95mm_HandSolder; MPN RC0603FR-0749R9L; not fitted
R304: 0R; R_0603_1608Metric_Pad0.98x0.95mm_HandSolder; MPN RC0603JR-070RL
R305, R321, R322: 0R; R_0603_1608Metric_Pad0.98x0.95mm_HandSolder; MPN RC0603JR-070RL; not fitted
R307, R310, R312, R313, R314, R315, R316, R317, R318, R319, R320, R323: 1k; R_0603_1608Metric_Pad0.98x0.95mm_HandSolder; MPN RC0603FR-071KL
SW301: PICO RUN; SW_TH_Tactile_Omron_B3F-100x; MPN B3F-1000
SW302: RESET; SW_TH_Tactile_Omron_B3F-100x; MPN B3F-1000
TP301: CLK; TestPoint_Keystone_5000-5004_Miniature; MPN 5000
TP302: RST_N; TestPoint_Keystone_5000-5004_Miniature; MPN 5000
U301: 74AUP1G74; SSOP-8_2.95x2.8mm_P0.65mm; MPN SN74AUP1G74DCTR
X301: 56MHz; Oscillator_SMD_Abracon_ASE-4Pin_3.2x2.5mm_HandSoldering; MPN SiT8008BI-22-33E-56.000000

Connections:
+3V3: C301.1, C302.1, J303.1, R301.1, R326.1, U301.7 (~PRE), U301.8 (VCC), X301.4 (Vdd); also elsewhere on the board
/Host/ADC_IOVDD: A301.32 (GPIO27_ADC1), C304.1, R324.2, R325.1
/Host/ADC_VDD: A301.31 (GPIO26_ADC0), C303.1, R323.2
/Host/CLK_EXT: J301.1 (In), R303.1, R305.1
/Host/CLK_OE: A301.19 (GPIO14), R301.2, X301.1 (OE)
/Host/CLK_SRC: R304.2, R305.2, R306.1, U301.1 (C)
/Host/CLK_XO: R302.2, R304.1
/Host/GP4: A301.6 (GPIO4), R321.1
/Host/GP5: A301.7 (GPIO5), R322.1
/Host/GP6: A301.9 (GPIO6), R313.1
/Host/GP7: A301.10 (GPIO7), R314.1
/Host/GP8: A301.11 (GPIO8), R315.1
/Host/GP9: A301.12 (GPIO9), R316.1
/Host/GP10: A301.14 (GPIO10), R317.2
/Host/GP11: A301.15 (GPIO11), R318.2
/Host/GP12: A301.16 (GPIO12), R319.2
/Host/GP13: A301.17 (GPIO13), R320.2
/Host/GP15: A301.20 (GPIO15), J303.2
/Host/GP20: A301.26 (GPIO20), J303.3
/Host/GP21: A301.27 (GPIO21), J303.4
/Host/GP22: A301.29 (GPIO22), J303.5
/Host/GP28: A301.34 (GPIO28_ADC2), J303.6
/Host/PICO_RX: A301.2 (GPIO1), R312.2
/Host/PICO_TX: A301.1 (GPIO0), R310.1
/Host/RST_D: R307.2, R308.1, SW302.1, U301.2 (D)
/Host/RST_REQ_N: A301.5 (GPIO3), R307.1
BUS_PICO: A301.4 (GPIO2), R326.2; also elsewhere on the board
CLK: R306.2, TP301.1; also elsewhere on the board
GND: A301.3 (GND), A301.8 (GND), A301.13 (GND), A301.18 (GND), A301.23 (GND), A301.28 (GND), A301.33 (AGND), A301.38 (GND), C301.2, C302.2, C303.2, C304.2, J301.2 (Ext), J302.3, J303.7, R303.2, R308.2, R325.2, SW301.1, SW302.2, U301.4 (GND), X301.2 (GND); also elsewhere on the board
GPIO_I0: R313.2; also elsewhere on the board
GPIO_I1: R314.2; also elsewhere on the board
GPIO_I2: R315.2; also elsewhere on the board
GPIO_I3: R316.2; also elsewhere on the board
GPIO_O0: R317.1; also elsewhere on the board
GPIO_O1: R318.1; also elsewhere on the board
GPIO_O2: R319.1; also elsewhere on the board
GPIO_O3: R320.1; also elsewhere on the board
IOVDD: R311.1, R324.1; also elsewhere on the board
unnamed: A301.30 (RUN), SW301.2
unnamed: R309.1, U301.5 (Q)
unnamed: R302.1, X301.3 (OUT)
PG_IO: U301.6 (~CLR); also elsewhere on the board
PICO_CS: A301.22 (GPIO17); also elsewhere on the board
PICO_MISO: A301.21 (GPIO16); also elsewhere on the board
PICO_MOSI: A301.25 (GPIO19); also elsewhere on the board
PICO_SCK: A301.24 (GPIO18); also elsewhere on the board
RST_N: R309.2, TP302.1; also elsewhere on the board
SCL: R322.2; also elsewhere on the board
SDA: R321.2; also elsewhere on the board
UART_RX: J302.2, R310.2, R311.2; also elsewhere on the board
UART_TX: J302.1, R312.1; also elsewhere on the board
VBUS: A301.40 (VBUS); also elsewhere on the board
VDD: R323.1; also elsewhere on the board

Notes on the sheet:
Raspberry Pi Pico H (RP2040) on two 1x20 sockets
GP0/GP1 UART to the chip, GP2 BUS_PICO, GP3 RST_REQ_N, GP6-9 gpio_in, GP10-13 gpio_out, GP14 CLK_OE, GP16-19 SPI0 to the PSRAM, GP26 VDD, GP27 IOVDD / 2, GP4/5 I2C (links not fitted).
Clock: 56 MHz oscillator (R304 fitted) or SMA J301 (R305), 33 Ohm at the chip
TW-E27: on 10 m the clock duty sets the I/Q balance. For a duty or bias trim drive J301 from a generator (3.3 V CMOS, the reset flip-flop needs 2.0 V high), R305 in, R304 out.
Reset: rst_n released on a clock edge (TW-E25), held low without IOVDD (TW-E31)
The Pico raises RST_REQ_N after it has loaded the PSRAM, checked VDD on GP26 and set BUS_PICO low. RESET pulls D low. U301 runs from +3V3: its clock input needs 2.0 V high.
UART: the Pico bridges USB to the chip, J302 for an external adapter
Host sends 2 stop bits (TW-E07). Firmware writes UART_TX_CPB = 485 (TW-E08). R310 limits the current an idle-high host pushes into an unpowered IOVDD.
Links: the Pico drives gpio_in and reads gpio_out through 1k, I2C sniffer links not fitted, supply readback
Bus owner default and spare Pico pins

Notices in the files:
README.md:
License: Solderpad Hardware License v2.1
pcb/analog.kicad_sch:
SPDX-FileCopyrightText: 2026 The TinyWhisper Team
SPDX-License-Identifier: Apache-2.0 WITH SHL-2.1
